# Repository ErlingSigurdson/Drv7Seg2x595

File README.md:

# Overview

**Drv7Seg2x595** is a single-class Arduino library for driving a multiplexed 7-segment display using
two daisy-chained 74HC595 shift register ICs.

## Concept

7-segment displays are simple, cheap and reliable data output devices. However, interfacing them with
a microcontroller (MC) requires appropriate software and, most commonly, additional hardware.

Typically, 7-segment displays come in models with 1 to 4 character positions (digits). Number of input pins for
any given model equals 8 + number of positions, thus 9 is the minimum and 12 is the maximum (duplicated pins count
as one). Driving such a display requires a number of individual signals equal to the number of the input pins:
* 8 signals to turn ON and OFF individual segments (including a dot segment, also known as a decimal point or DP).
* 1 to 4 signals to turn ON and OFF whole positions.

Due to significant number of required signals, output-extending devices, such as output shift registers, are commonly
used. **74HC595**, sometimes simply called **595**, is a widely used 8-bit serial-in, parallel-out (SIPO) shift register
integrated circuit (IC) commonly employed to drive 7-segment displays. Despite being a SIPO register primarily, it also
features an auxiliary serial output that allows for **daisy-chaining**: connecting multiple 595s in such a way that
the serial output of the previous IC goes to the serial input of the next one and all ICs in the chain share the same
**clock** and **latch** signals. Two daisy-chained 595s form a 16-bit shift register, which is sufficient for
controlling any typical 7-segment display.

The API provided by this library allows for control over 1 to 4 character positions. The number of positions to be
used must be specified during the driver configuration.

## Control bytes

This library assumes that the 16-bit register consists of two bytes with distinct roles:
* **segment byte** (**`seg_byte`**) controls individual display segments to form recognizable symbols (glyphs).
* **position byte** (**`pos_byte`**) controls whole character positions and thus determines where the next segment
pattern (defined by `seg_byte`) will be output. 1 to 4 bits out of 8 are used, the rest are not connected (NC).

The API provided by this library allows for any order of `seg_byte` and `pos_byte` placement within the register,
that is, any of these bytes may be either upper or lower byte. The byte order must be specified during the driver
configuration.

## Multiplexing

This library relies on **multiplexing**: a way of driving a multi-digit 7-segment display by turning on only one
character position at a time in quick succession, in a cycle. Because the multiplexing cycle runs faster than
the eye can follow, all positions appear to be lit continuously, even though only one is actually turned on at
any given moment.

This approach greatly simplifies the circuit because it doesn't rely on a separate set of segment-control outputs
for every position and instead utilizes the single set of segment-control outputs shared by **all** positions
(the defined segment pattern shows up only on the intended position anyway, because only that position will be
turned on at the appropriate moment).

### Ghosting and countermeasures

Advantages of multiplexing come with an unwanted side effect called **ghosting**: segments can seem to have a faint,
"ghost-like" glow on positions that are supposed to be off. To avoid this effect, the library utilizes the anti-ghosting
techniques that involve retention of a currently output glyph on a respective position for a short period of time.
Duration of the said period can be fine-tuned by the library user via the library's API.

The library's anti-ghosting logic is based on a non-blocking, `micros()`-based timer. No blocking, `delay()`-based
timers are used.

## Position switching

Every character position is turned on (powered) by either setting or clearing the `pos_byte` bit specified during
the driver configuration. It can be done because the bit value determines the digital output level (either high or low)
of the corresponding parallel output pin, which makes it possible to source/sink current from/to that pin.
The resulting current may be used to power the position directly or via a switching device, such as a transistor.
The latter approach is far more common, since 595's capacity for sourcing/sinking current for a whole set of 8 LEDs gets
close to or exceeds its electrical limitations.

Depending on the display type (whether it's a common-cathode or a common-anode device) and the switching device type
(whether it's an active-high device, like an NPN BJT or an N-channel MOSFET, or an active-low device, like a PNP BJT or
a P-channel MOSFET), positions will be turned on either by high or low digital output level. The API provided by this
library supports both variants. The switching type (active-high or active-low) must be specified during the driver
configuration.

## Data transfer (shifting)

The driver implemented by this library uses either bit-banging or SPI for shifting the data into the shift register.
If you choose bit-banging, the driver will use whatever GPIO pins you assign to it. If you choose SPI, the driver will
use the default SPI instance (although support for non-default and multiple SPI instances may be added later).

## Reference schematic

Here's a typical circuit diagram for the described arrangement (assumes a common-cathode display):

.png)

For convenience, the example sketch default constant values corresponds to the circuit diagram provided here.

Wiring for a common-anode display is almost identical, the only difference being that the transistors' emitters
should connect to the display's common pins and their collectors should connect to the circuit's positive rail (VCC).

The wiring in your circuit **may** differ from the provided schematic to some degree, and the library will still be
applicable as long as your circuit complies with the premise of the `seg_byte` and `pos_byte` distinct roles.

### Notes on the reference schematic

* Power your 595s with the same voltage your MC runs on.
* Transistors Q1..Q4 are intended to be general-purpose NPN BJTs such as MMBT3904 (assumed by the reference PCB design,
see below), 2N3904, 2N4401, 2N2222, or BC548. You can even use a [KT315](https://ru.wikipedia.org/wiki/%D0%9A%D0%A2315),
comrade.
* If the display segment LEDs are too bright, or if you notice visible brightness changes when the DP blinks, increase
the R0..R7 resistor values to around 470-680 Ω. This is especially advisable if your 595s are powered from a 5 V supply.

## API usage

Include the library:
```cpp
#include <Drv7Seg2x595.h>    // Arduino style.
//#include "Drv7Seg2x595.h"  // Generic embedded programming style.
```

### Driver configuration

Choose **one** of the following variants.

Bit-banging:
```cpp
// Prototype.
int32_t begin_bb(ByteOrder byte_order,           // Whether seg_byte or pos_byte will be an upper byte.
                 PosSwitchType pos_switch_type,  // Whether high or low output level turns on a character position.
                 uint32_t data_pin,              // The pin that outputs the next bit value to be shifted.
                 uint32_t latch_pin,             // The pin that propagates the shifted data to the output register.
                 uint32_t clock_pin,             // The pin that commands the next bit value to be shifted.
                 PosBit pos_1_bit,               // Number of the pos_byte bit that will control the 1st position.
                 PosBit pos_2_bit,               // Number of the pos_byte bit that will control the 2nd position.
                 PosBit pos_3_bit,               // Number of the pos_byte bit that will control the 3rd position.
                 PosBit pos_4_bit                // Number of the pos_byte bit that will control the 4th position.
                );

// Example call.
Drv7Seg.begin_bb(Drv7SegPosByteFirst,  // Other option is Drv7SegSegByteFirst.
                 Drv7SegActiveHigh,    // Other option is Drv7SegActiveLow.

                 /* Digital output pins you want to use for driving the display.
                  * Pin numbers must correspond to the pin numbering specified
                  * by the Arduino core you're using.
                  */
                 16, 17, 18,

                 /* Valid arguments are Drv7SegPosBitN, where N is in the 0..7 range (MSB to LSB of pos_byte).
                  *
                  * The first one of these arguments (1st position bit) is required.
                  * Subsequent arguments are optional.
                  * The driver will be configured to control the number of positions
                  * equal to the number of arguments that weren't omitted.
                  */
                 Drv7SegPosBit7,  // This parameter is required.
                 Drv7SegPosBit5,  // This parameter is optional.
                 Drv7SegPosBit3,  // This parameter is optional.
                 Drv7SegPosBit1   // This parameter is optional.
                );
```

SPI with default pins:
```cpp
/* Mostly identical to the bit-banging variant, but only the latch pin needs to be specified
 * (the default MOSI pin must be used as a data pin and the default SCK pin must be used as a clock pin).
 */

// Example call.
Drv7Seg.begin_spi(...
                  LATCH_PIN,
                  ...
                 );
```

SPI with custom pins:
```cpp
/* Mostly identical to the bit-banging variant, but the data pin role goes to
 * the specified MOSI pin and the clock pin role goes to the specified SCK pin.
 */

// Example call.
Drv7Seg.begin_spi_custom_pins(...
                              MOSI_PIN,
                              LATCH_PIN,
                              SCK_PIN,
                              ...
                             );
```

### Status check

Get the driver configuration status (check if it was configured successfully):
```cpp
int32_t drv_config_status = Drv7Seg.get_status();
// Loop the error output if the driver configuration was unsuccessful.
if (drv_config_status < 0) {  // If an error is detected.
    while(true) {
        Serial.print("Error: driver configuration failed, error code ");
        Serial.println(drv_config_status);
        delay(INTERVAL);
    }
}
```
You can also check the value returned by `begin_*()` instead of calling `get_status()`.

### Output

Assign the glyphs you want to output to each character position:
```cpp
// Prototype.
int32_t set_glyph_to_pos(uint8_t seg_byte,  // A byte that corresponds to the glyph to be output.
                         Pos pos            // A number of the position the glyph must be output on.
                        );

// Example call (single).
Drv7Seg.set_glyph_to_pos(
                         0b00010001,  // Depending on wiring, may represent character '1'.

                         /* Valid arguments are Drv7SegPosN, where
                          * N => 1
                          * and
                          * N <= the number of positions the driver was configured to use.
                          */
                          Drv7SegPos1
                        );

/* Example calls (typical implementation).
 *
 * Make recurrent calls in quick succession for all positions your driver was configured to use.
 */
Drv7Seg.set_glyph_to_pos(seg_byte_minutes_tens, Drv7SegPos1);
Drv7Seg.set_glyph_to_pos(seg_byte_minutes_ones, Drv7SegPos2);
Drv7Seg.set_glyph_to_pos(seg_byte_seconds_tens, Drv7SegPos3);
Drv7Seg.set_glyph_to_pos(seg_byte_seconds_ones, Drv7SegPos4);
```

Commence the actual output:
```cpp
// Call it inside the loop() function.
Drv7Seg.output_all();
```

If you want a more fine-grained control over output, you can use a lower level method.
Using it will override the glyph assignment done with `set_glyph_to_pos()` calls.
```cpp
// Prototype.
int32_t output(uint8_t seg_byte,  // A byte that corresponds to the glyph to be output.
               Pos pos            // A number of the position the glyph must be output on.
              );

// Example call (single).
Drv7Seg.output(
               0b00010001,  // Depending on wiring, may represent character '1'.

               /* Valid arguments are Drv7SegPosN, where
                * N => 1
                * and
                * N <= the number of positions the driver was configured to use.
                */
               Drv7SegPos1,
              );

/* Example calls (typical implementation).
 *
 * Make recurrent calls in quick succession for all positions your driver was configured to use.
 */
Drv7Seg.output(seg_byte_minutes_tens, Drv7SegPos1);
Drv7Seg.output(seg_byte_minutes_ones, Drv7SegPos2);
Drv7Seg.output(seg_byte_seconds_tens, Drv7SegPos3);
Drv7Seg.output(seg_byte_seconds_ones, Drv7SegPos4);
```

### Anti-ghosting

Ghosting prevention involves retention of a currently displayed glyph on a corresponding position for a short period
of time. The duration of such period has a reasonable default of 600 microseconds, but you can override it.
```cpp
/* If you encounter ghosting, random flickering, or glyphs appear too dim or show inconsistent brightness,
 * try passing a higher value (about 1000 to 4000).
 * If you encounter constant flickering, try passing a lower value (about 10 to 400).
 */
Drv7Seg.set_anti_ghosting_retention_duration(1000);
```

Refer to `Drv7Seg2x595.h` for more API details.

## Special cases

* **Multiple drivers**. You can create additional instances of `Drv7Seg2x595Class` and use them for driving multiple
displays, but you shouldn't employ SPI by more than one instance at a time.

* **Single-digit displays**. With a single-position display there's usually no purpose in a switchable signal that
turns the only character position ON and OFF (all control job can be done by `seg_byte` alone), nor there's a need for
multiplexing. Still, you can use this library to control a single-digit display in a pinch. You can either:
    - assign a single position bit during the driver configuration and use that bit to control your only position (in this
case the multiplexing logic will still be applied, but the single position will always be the one to be turned on next);
    - ignore `pos_byte` completely and power your display directly by connecting it to GND or VCC, according to the display
type. You will still have to pass a single position bit argument during the driver configuration to comply with
the library logic, but its particular value becomes irrelevant (pick `Drv7SegPosBit0`, it'll be fine).

* **Ignoring certain digits**. If you, for instance, have a 4-position display and for some reason you want to use
only positions 2 and 3, it's completely OK, you can do that using this library. Pass two position bits during the driver
configuration: one for the 2nd physical position (it'll correspond to `Drv7SegPos1` within the library logic) and
another one for the 3rd physical position (it'll correspond to `Drv7SegPos2` within the library logic).

## Dependencies

* `SPI.h` library implementation for the Arduino core and the board (device) you're using.
It is available for most major Arduino cores, although it isn't guaranteed that every single Arduino core in the world
will have it as well. In an unlikely case when it is not implemented for your Arduino core or device, you can still use
this library's bit-banging mode, but in order to avoid compilation errors you'll have to manually comment out the
`#define DRV7SEG2X595_SPI_PROVIDED_ASSUMED` preprocessor directive in `Drv7Seg2x595.h`.

* **SegMap595** library (available from Arduino Library Manager, also see links below) is used in the example sketch
in order to simplify byte mapping, but aside from that it's not a prerequisite for using `Drv7Seg2x595.h`.

## Compatibility

The library works with any Arduino-compatible MC capable of bit-banging or SPI data transfer.

Availability of the configuration variant that takes custom-assigned SPI pins relies on the capabilities of a given MC
and the corresponding `SPI.h` implementation. As of the last update to this library, this variant is only available for
ESP32 and STM32 MC families.

### PCB design and rich circuit diagram

You may opt to use the [KiCAD](https://www.kicad.org/) [project](extras/kicad/) provided with this library to build
a DIY hardware driver compliant with the library's premises and the reference circuit. The project was created in
KiCAD 9.0.

[(Click here to view full-size image)](extras/images/pcb_view_w_footprints_full_size.png)

Using the provided design is totally **optional**. This library is built with flexibility in mind and does **NOT**
depend on a single particular wiring.

## To-do list

* Add support for using non-default and multiple SPI instances.
* Make the reference PCB layout more compact.

## Licensing

* The software part of this library, as well as its documentation, is licensed under the **MIT License**
(see `LICENSE` [here](LICENSE)).
* All hardware-related files in this library, including illustrations, are licensed under the **CERN-OHL-P v2**
(see `extras/kicad/LICENSE_HARDWARE` [here](extras/kicad/LICENSE_HARDWARE)).

## Links

### This library
* [Primary repository on GitHub](https://github.com/ErlingSigurdson/Drv7Seg2x595)
* [Backup repository on GitFlic](https://gitflic.ru/project/efimov-d-v/drv7seg2x595)
* [Backup repository on Codeberg](https://codeberg.org/ErlingSigurdson/Drv7Seg2x595)

### SegMap595
* [Primary repository on GitHub](https://github.com/ErlingSigurdson/SegMap595)
* [Backup repository on GitFlic](https://gitflic.ru/project/efimov-d-v/segmap595)
* [Backup repository on Codeberg](https://codeberg.org/ErlingSigurdson/SegMap595)

### Drv7SegQ595
A derivative (a fork) of this library. Uses a set of GPIO-driven transistors instead of `pos_byte`.
* [Primary repository on GitHub](https://github.com/ErlingSigurdson/Drv7SegQ595)
* [Backup repository on GitFlic](https://gitflic.ru/project/efimov-d-v/Drv7SegQ595)
* [Backup repository on Codeberg](https://codeberg.org/ErlingSigurdson/Drv7SegQ595)

## Contact details

**Maintainer** — Dmitriy Efimov aka Erling Sigurdson
* <efimov-d-v@yandex.ru>
* <erlingsigurdson1@gmail.com>
* Telegram: @erlingsigurdson

Your feedback and pull requests are welcome.

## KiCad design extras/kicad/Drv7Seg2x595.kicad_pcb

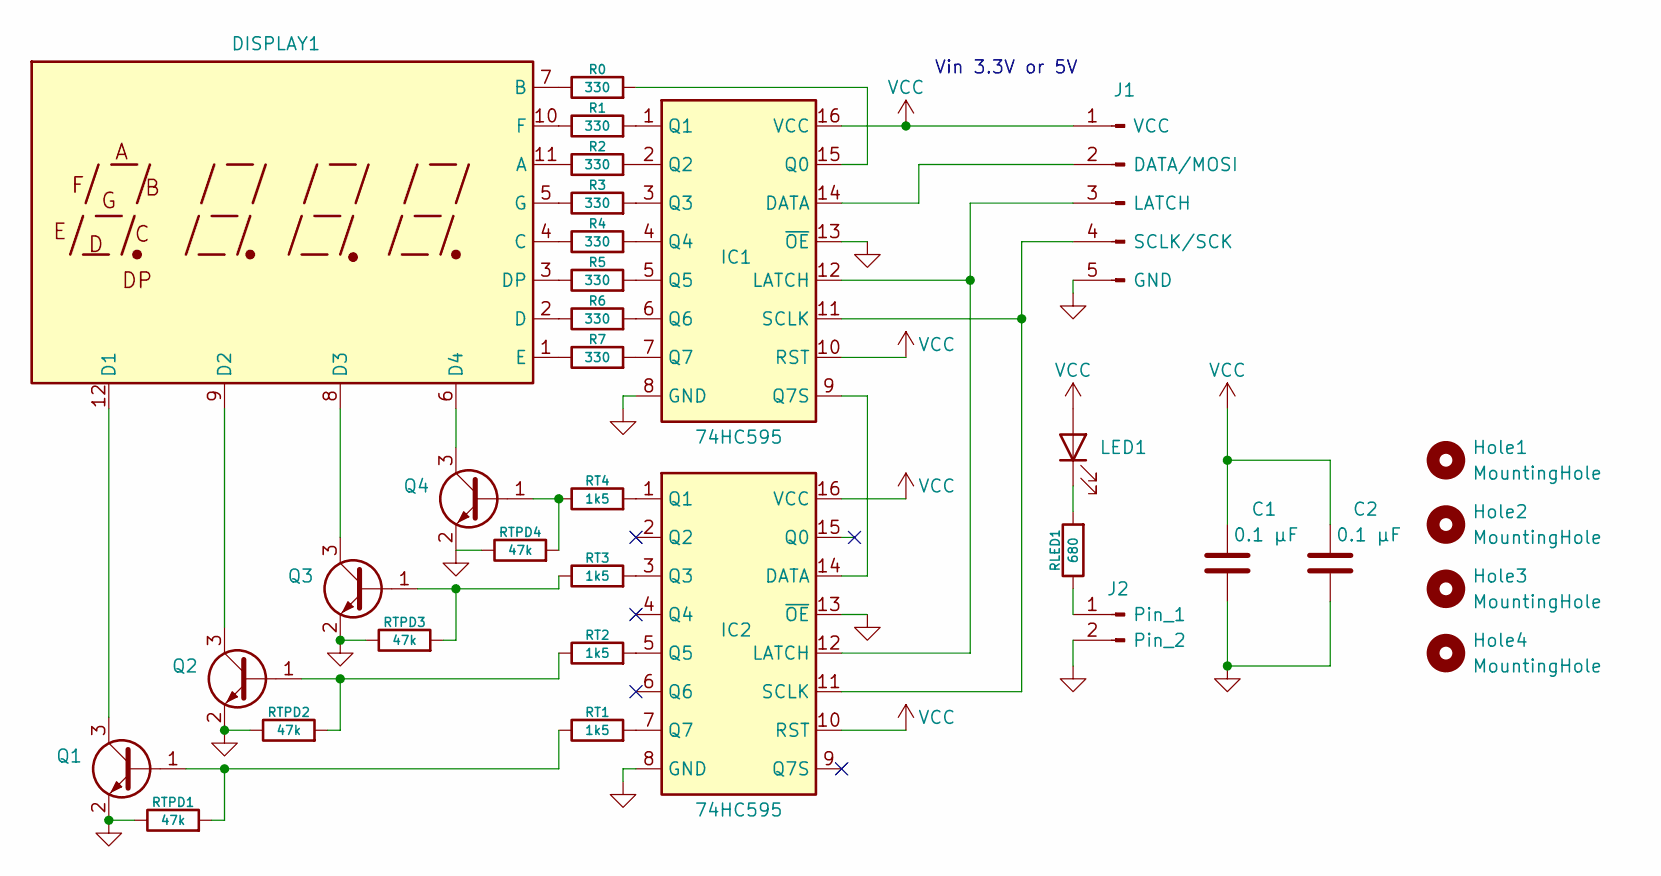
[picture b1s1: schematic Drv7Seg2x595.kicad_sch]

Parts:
C1, C2: 0.1 μF; C_0805_2012Metric_Pad1.18x1.45mm_HandSolder
D1: LED1; LED_0805_2012Metric_Pad1.15x1.40mm_HandSolder
DISPLAY1: display_7seg_4d; display_7seg_4d_0.56in
Hole1, Hole2, Hole3, Hole4: MountingHole; MountingHole_3mm
IC1, IC2: 74HC595; DIP-16_W7.62mm
J1: INTERFACE; PinHeader_1x05_P2.54mm_Horizontal
J2: PWR_LED_JMP; PinHeader_1x02_P2.54mm_Horizontal
Q1, Q2, Q3, Q4: MMBT3904; SOT-23
R0, R1, R2, R3, R4, R5, R6, R7: 330; R_0805_2012Metric_Pad1.20x1.40mm_HandSolder
RLED1: 680; R_0805_2012Metric_Pad1.20x1.40mm_HandSolder
RT1, RT2, RT3, RT4: 1k5; R_0805_2012Metric_Pad1.20x1.40mm_HandSolder
RTPD1, RTPD2, RTPD3, RTPD4: 47k; R_0805_2012Metric_Pad1.20x1.40mm_HandSolder

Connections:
GND: C1.2, C2.1, IC1.8 (GND), IC1.13 (~OE), IC2.8 (GND), IC2.13 (~OE), J1.5 (GND), J2.2, Q1.2 (E), Q2.2 (E), Q3.2 (E), Q4.2 (E), RTPD1.1, RTPD2.1, RTPD3.1, RTPD4.1
unnamed: D1.1 (K), RLED1.2
unnamed: DISPLAY1.11 (A), R2.1
unnamed: DISPLAY1.7 (B), R0.1
unnamed: DISPLAY1.4 (C), R4.1
unnamed: DISPLAY1.12 (D1), Q1.3 (C)
unnamed: DISPLAY1.9 (D2), Q2.3 (C)
unnamed: DISPLAY1.8 (D3), Q3.3 (C)
unnamed: DISPLAY1.6 (D4), Q4.3 (C)
unnamed: DISPLAY1.2 (D), R6.1
unnamed: DISPLAY1.3 (DP), R5.1
unnamed: DISPLAY1.1 (E), R7.1
unnamed: DISPLAY1.10 (F), R1.1
unnamed: DISPLAY1.5 (G), R3.1
unnamed: IC1.14 (DATA), J1.2 (DATA/MOSI)
unnamed: IC1.12 (LATCH), IC2.12 (LATCH), J1.3 (LATCH)
unnamed: IC1.15 (Q0), R0.2
unnamed: IC1.1 (Q1), R1.2
unnamed: IC1.2 (Q2), R2.2
unnamed: IC1.3 (Q3), R3.2
unnamed: IC1.4 (Q4), R4.2
unnamed: IC1.5 (Q5), R5.2
unnamed: IC1.6 (Q6), R6.2
unnamed: IC1.7 (Q7), R7.2
unnamed: IC1.9 (Q7S), IC2.14 (DATA)
unnamed: IC1.11 (SCLK), IC2.11 (SCLK), J1.4 (SCLK/SCK)
unnamed: IC2.1 (Q1), RT4.2
unnamed: IC2.3 (Q3), RT3.2
unnamed: IC2.5 (Q5), RT2.2
unnamed: IC2.7 (Q7), RT1.2
unnamed: J2.1, RLED1.1
unnamed: Q1.1 (B), RT1.1, RTPD1.2
unnamed: Q2.1 (B), RT2.1, RTPD2.2
unnamed: Q3.1 (B), RT3.1, RTPD3.2
unnamed: Q4.1 (B), RT4.1, RTPD4.2
VCC: C1.1, C2.2, D1.2 (A), IC1.10 (RST), IC1.16 (VCC), IC2.10 (RST), IC2.16 (VCC), J1.1 (VCC)

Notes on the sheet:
Vin 3.3V or 5V

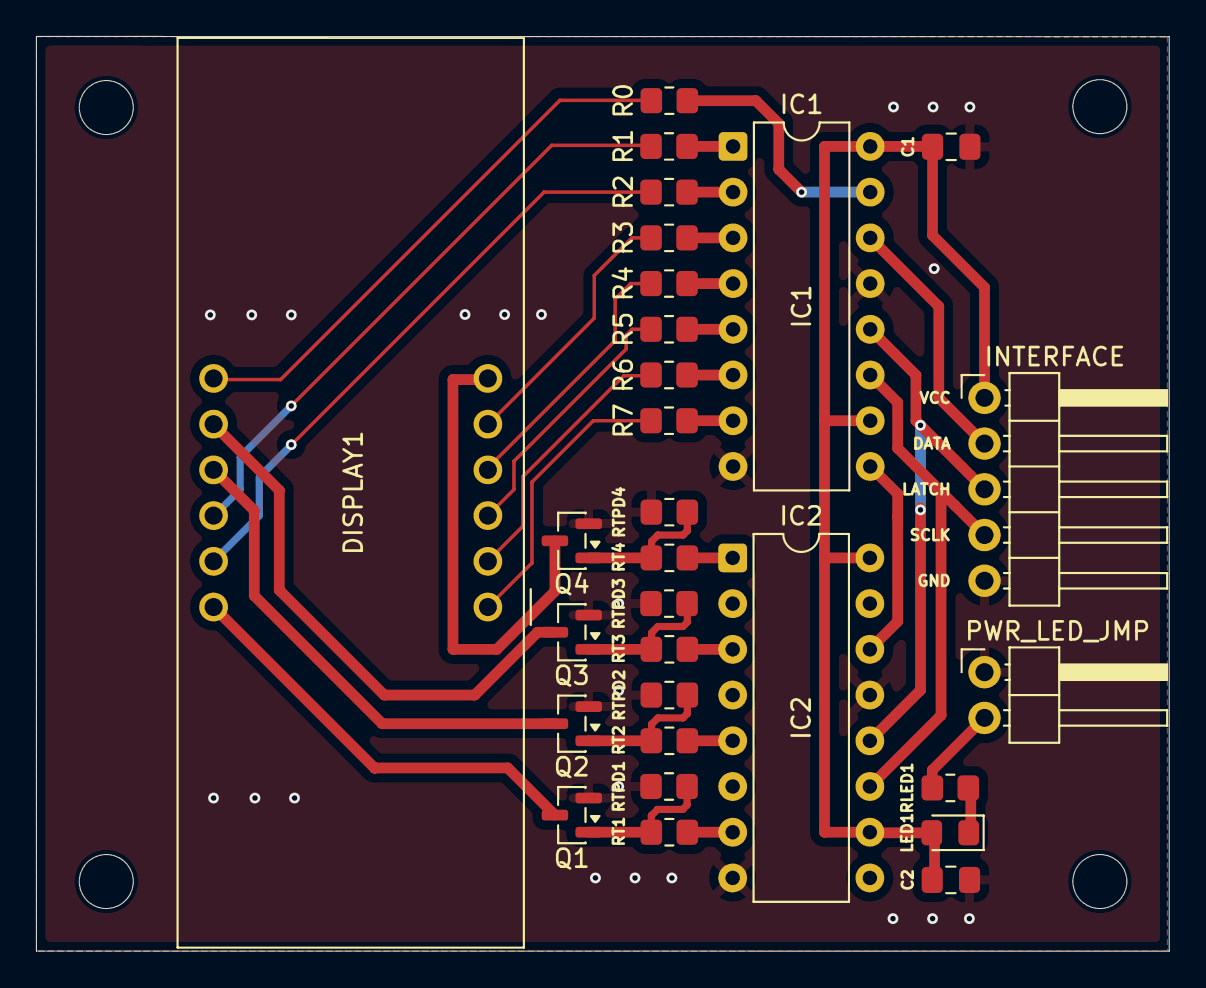
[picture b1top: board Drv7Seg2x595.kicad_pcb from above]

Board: 2 copper layers, 62.9 x 50.8 mm, 33 parts (0 on the bottom side), 36 nets.

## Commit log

2025-12-21 Update default anti-ghosting retention duration value and relevant comments.
2025-12-21 Move SMD caps, power indicator LED and its resistor behind the headers' line.
2025-12-21 Restyle interface header labels + move mounting holes symbols on schematic a bit.
2025-12-21 Update schematic image.
2025-12-21 Return mounting holes (deleted them accidentally while taking a screenshot).
2025-12-21 Update PCB 3D rendering image.
2025-12-21 Update library version in library.properties.
2025-12-21 Update README: add mention of Drv7SegQ595 derivative.
2025-12-21 Make steps towards more compact PCB.
2025-12-22 Make more steps towards more compact PCB, but keep components on one side yet.
2025-12-22 Update README: update note on employing SPI by multiple class instances.
2025-12-29 Update according to SegMap595 update + add preprocessor conditional for Serial.begin().
2026-01-03 Update example sketch to keep up with SegMap595 library updates.
2026-01-13 Apply standard delimiter style.
2026-01-14 Fix spacing in header file docs.

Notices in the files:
README.md:
Licensing:
The software part of this library, as well as its documentation, is licensed under the **MIT License
(see `LICENSE` [here](LICENSE)).
All hardware-related files in this library, including illustrations, are licensed under the **CERN-OHL-P v2
(see `extras/kicad/LICENSE_HARDWARE` [here](extras/kicad/LICENSE_HARDWARE)).
extras/kicad/Drv7Seg2x595.kicad_pcb:
Copyright (c) 2025 Dmitriy Efimov aka Erling Sigurdson
Licensed under CERN-OHL-P v2
